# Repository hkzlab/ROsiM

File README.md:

# ROsiM - ROM simulator

## Introduction

The ROsiM is a ROM simulation / emulation board: it uses two 512k/8bit SRAM chips to simulate an 8 or 16 bit ROM (up to 512k bytes or 512k words in size).

The board is based around an ATMega328P chip @20Mhz, controlled via serial connection.

I made this out of my personal need of a simple way to quickly test ROM images on boards I repair/hack/build. Often, these boards use big 16bit EPROMs and the projects I found around did not cater to my needs.

The idea is to use this bare board and then "pods" that attach to the two 40pin header and adapt it to simulate various types of ROMs.

**WARNING:** While I might help you with quick questions, there is NOT going to be hand-holding for this one.

### Caveat Emptor!

I have currently built and tested revision 1.3 of this board. The following fixes must be implemented to make it usable:

- Wire the VCCIO pad from FT232RL to VCC and do NOT short it to 3.3v. This is already fixed in board rev. 1.4

The following mod is optional but encouraged for safety, and have been implemented for revision 1.4:

- Cut the trace between pin 1 of USB connector (Vcc) and F1, and insert a BAT48 SOD123 diode, cathode towards F1. This will protect your USB port if the board gets externally powered.
- Lower F1 max current to 200mA

## Board

This board is designed around relatively cheap through hole (with a few exceptions) components, and should be buildable by anyone with basic soldering skills.

You'll need a way to program your 328P MCU with the bootloader (you can then load the firmware via serial port).

I recommend [optiboot](https://github.com/Optiboot/optiboot). Remember to set the AVR frequency to 20Mhz and baudrate to 115200bps. I might provide prebuilt binaries of this in the future.

### Bill of Materials

**TODO**

### Connections

#### J1 - ISP 6 pin header

This is used for in-circuit programming of the MCU. You won't really use after burning the bootloader to the chip. You can leave this out if you pre-program the ATMega.

#### J2 - USB Type B female

Connect your USB cable here. It will appear as an FTDI serial port to the host.

The Interface runs at 230400bps 8-n-1. The protocol is mainly ASCII based, but meant to be used with an external software.

#### J3 - Barrel jack for power

Connect your DC power supply here, **center tip positive**.
Anything between 7 to 9V will be good, 12V will work, but the regulator might get hotter. 500mA should be enough.

#### J4 - Address header

A 40 pin header:

- Odd pins 1 thru 37 on the left side will bring out the address lines (A0-A18).
- Pin 39 will be this board's VCC.
- All even pins on the right are GND.

#### J5 - Data header

A 40 pin header: 

- Odd pins 1 thru 31 on the left side will bring out the data lines (D0-D15).
- Pin 33 will be the /CE signal input.
- Pin 35 will be the /OE signal input.
- Pin 39 will be this board's VCC.
- All even pins on the right are GND.

#### J6 - /RESET header

An active-low OC signal will be present on this header. You can use to pilot the /RESET of your target board.

Solder an arc of rigid wire on this one, so you can attach a small crocodile clip to it.

#### J7 - RESET header

An active-high signal (either high or disconnected) will be present on this header.

Solder an arc of rigid wire on this one, so you can attach a small crocodile clip to it.
## Software

While this board can be controlled directly via a simple serial terminal, it is advised to use a client software that supports the following protocol, like the [ROsiM Loader](https://github.com/hkzlab/ROsiM_Loader).

### Protocol

The **Remote Control** protocol is pretty simple and ASCII based. It supports 12 commands, each with its own syntax and response.

String `CMD_ERR` will be sent in case the command is not recognized, string `CMD_INV` will be sent in case the command cannot be executed at this time.

#### RESET

- Syntax: `>K<`
- Response: none

Forces the reset by watchdog of the ROsiM.

#### MODEL

- Syntax: `>M<`
- Response: `[M xx]`

Returns the current model of the board in hex. 

#### ADDRESS

- Syntax: `>A 00xxxxxx<`
- Response: `[A 00xxxxxx]`

Specifies the start address for the next read/write commands.
The address must be specified in hex, and a mask of 0x7FFFF will be applied to it.

#### WRITE

- Syntax: `>W xxxx<`
- Response: `[W xxxx]`

The SRAM must be in WRITE mode and the board switched to INTERNAL, otherwise the response `CMD_INV` will be sent.

`xxxx` is the data to write on SRAM at the current address in hex format.
Once the write completes, the **address will automatically increment by 1**.

#### READ

- Syntax: `>R<`
- Response: `[R xxxx]`

The SRAM must be in READ mode and the board switched to INTERNAL, otherwise the response `CMD_INV` will be sent.

`xxxx` is the data written at the current address in hex format. Once the read completes, the **address will automatically increment by 1**.

#### EXTERNAL RESET

- Syntax: `>E y<` where `y` can be `0` or `1`
- Response: `[E y]`

Enables (`1`) or disables (`0`) the external RESET signal to the target board.

#### INTERNAL/EXTERNAL SWITCH

- Syntax: `>S y<` where `y` can be `0` or `1`
- Response: `[S y]`

To execute this command, the SRAM must be in READ mode, otherwise the response `CMD_INV` will be sent.
Sets the board to INTERNAL (`1`) or EXTERNAL (`0`) mode. EXTERNAL mode will enable the drivers that communicate through the external address/data/control lines.

#### READ/WRITE SWITCH

- Syntax: `>X y<` where `y` can be `0` or `1`
- Response: `[X y]`

To execute this command, the board must be in INTERNAL mode, otherwise the response `CMD_INV` will be sent.
Sets the SRAM to READ (`1`) or WRITE (`0`) mode.

#### VIEW

- Syntax: `>V<`
- Response: `[V 00xxxxxx yy]`

This command will print out the current address in hex format (`00xxxxxx`) and a mask (`yy`) in hex format that contains:

- bit 0: INTERNAL/EXTERNAL state
- bit 1: READ/WRITE state
- bit 2: EXTERNAL RESET state

#### DEFAULTS

- Syntax: `>D<`
- Response: `[D]`

Will revert the board state to the following state:

- INTERNAL
- SRAM in READ mode
- EXTERNAL RESET disabled

The selection of the EXTERNAL RESET logic will **NOT** be restored by this command and will remain set to the current state.

#### TEST

- Syntax: `>T<`
- Response: `[T xx]`

Resets the board to defaults then executes a test on the SRAMs by writing patterns of data in them and reading them back.

The output can be:

- `00` test was completed successfully
- `01` test failed while writing the first pattern (`0xAA55`)
- `02` test failed while writing the first pattern (`0x55AA`)
- `03` the test failed while writing the incremental pattern

#### XMODEM

- Syntax: `>O x<`
- Response: `[O yy]`

Starts an XMODEM transfer of a binary file into the SRAM.

`x` can be:

- `0` The file will be considered an 8-bit dump, the highest 8 bits of the SRAM will be set to `0x00`, only the lower 8 bits will be set.
- `1` The file will be considered a 16-bit dump, and the data will be loaded into the SRAM in words. ODD bytes in the dump will end up in the high byte of the SRAM, EVEN bytes will end up in the low byte of the SRAM.
- `2` The file will be considered a **byte swapped** 16-bit dump, and the data will be loaded into the SRAM in words. EVEN bytes in the dump will end up in the high byte of the SRAM, ODD bytes will end up in the low byte of the SRAM.

`yy` will be:

- `00` for a failed transfer.
- `01` for a successful transfer.

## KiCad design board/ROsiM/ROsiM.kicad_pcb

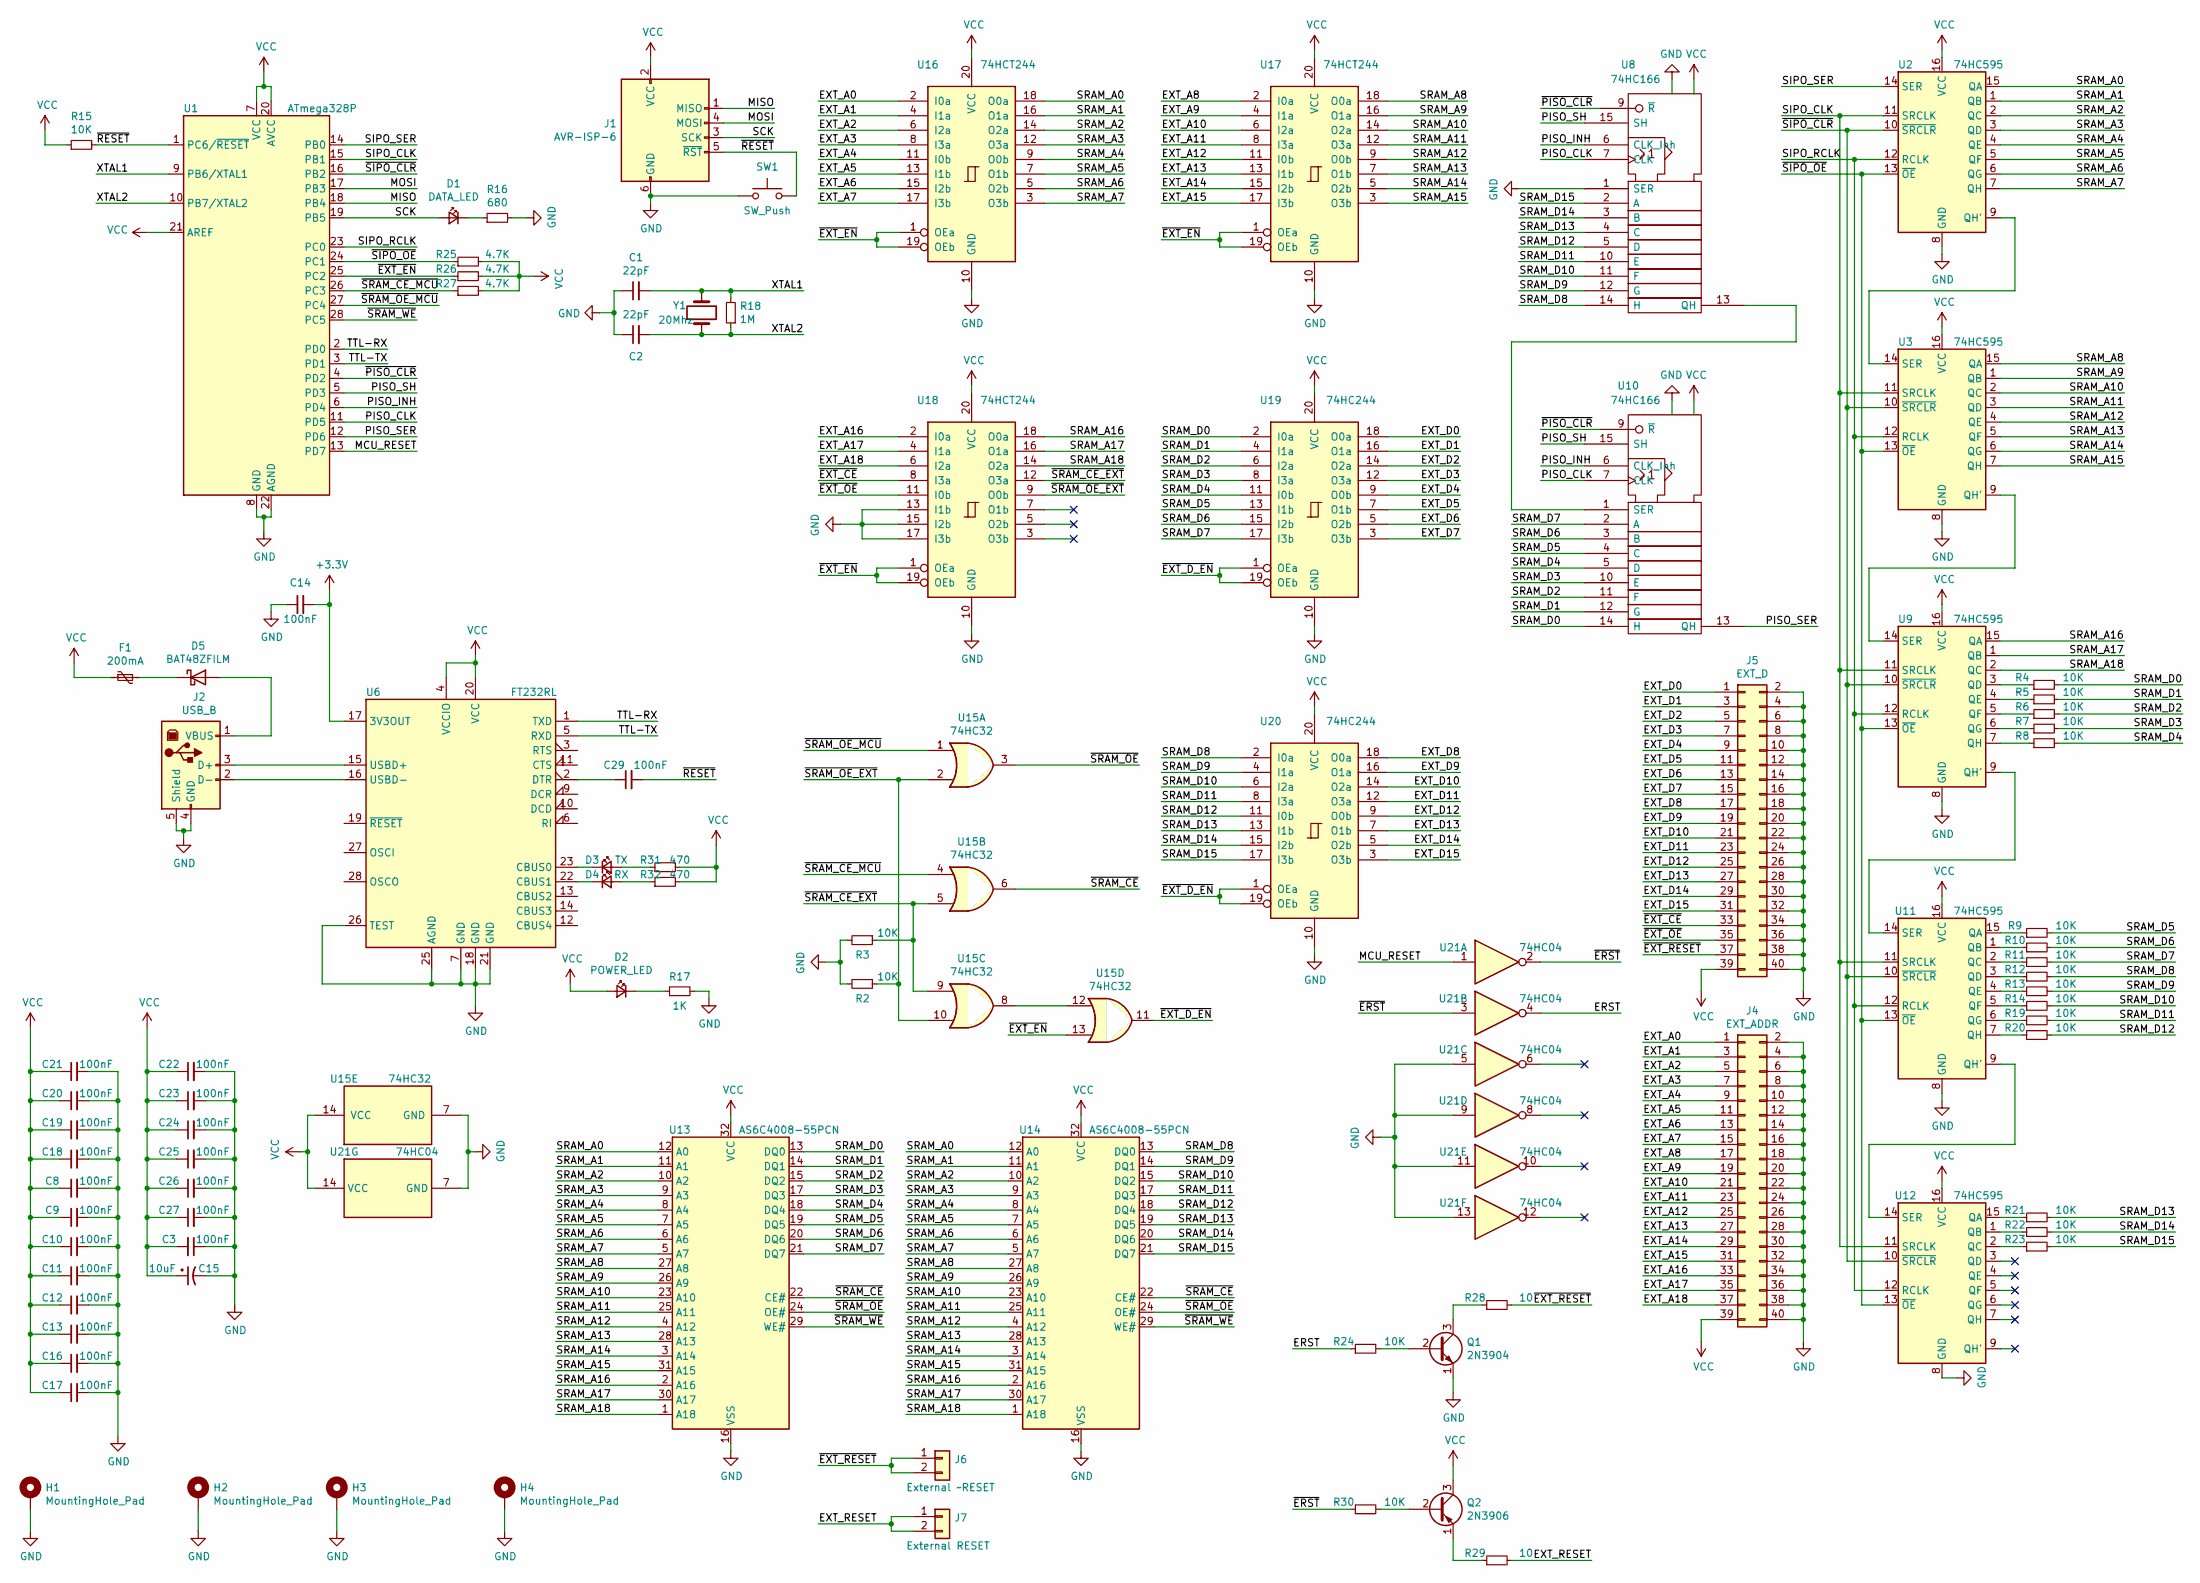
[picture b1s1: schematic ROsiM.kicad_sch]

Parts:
C1, C2: 22pF; C_Disc_D3.0mm_W2.0mm_P2.50mm
C3, C8, C9, C10, C11, C12, C13, C14, C16, C17, C18, C19, C20, C21, C22, C23, C24, C25, C26, C27, C29: 100nF; C_Disc_D3.4mm_W2.1mm_P2.50mm
C15: 10uF; CP_Radial_D5.0mm_P2.50mm
D1: DATA_LED; LED_D2.0mm_W4.8mm_H2.5mm_FlatTop
D2: POWER_LED; LED_D2.0mm_W4.8mm_H2.5mm_FlatTop
D3: TX; LED_D2.0mm_W4.8mm_H2.5mm_FlatTop
D4: RX; LED_D2.0mm_W4.8mm_H2.5mm_FlatTop
D5: BAT48ZFILM; D_SOD-123
F1: 200mA; Fuse_1206_3216Metric
H1, H2, H3, H4: MountingHole_Pad; MountingHole_2.7mm_M2.5_ISO7380_Pad
J1: AVR-ISP-6; IDC-Header_2x03_P2.54mm_Vertical
J2: USB_B; USB_B_Lumberg_2411_02_Horizontal
J4: EXT_ADDR; PinHeader_2x20_P2.54mm_Vertical
J5: EXT_D; PinHeader_2x20_P2.54mm_Vertical
J6: External ~RESET; PinSocket_1x02_P2.54mm_Vertical
J7: External RESET; PinSocket_1x02_P2.54mm_Vertical
Q1: 2N3904; TO-92_Inline
Q2: 2N3906; TO-92_Inline
R2, R3, R4, R5, R6, R7, R8, R9, R10, R11, R12, R13, R14, R15, R19, R20, R21, R22, R23, R24, R30: 10K; R_Axial_DIN0204_L3.6mm_D1.6mm_P7.62mm_Horizontal
R16: 680; R_Axial_DIN0204_L3.6mm_D1.6mm_P7.62mm_Horizontal
R17: 1K; R_Axial_DIN0204_L3.6mm_D1.6mm_P7.62mm_Horizontal
R18: 1M; R_Axial_DIN0204_L3.6mm_D1.6mm_P7.62mm_Horizontal
R25, R26, R27: 4.7K; R_Axial_DIN0204_L3.6mm_D1.6mm_P7.62mm_Horizontal
R28, R29: 10; R_Axial_DIN0204_L3.6mm_D1.6mm_P7.62mm_Horizontal
R31, R32: 470; R_Axial_DIN0204_L3.6mm_D1.6mm_P7.62mm_Horizontal
SW1: SW_Push; SW_PUSH_6mm
U1: ATmega328P; DIP-28_W7.62mm
U2, U3, U9, U11, U12: 74HC595; DIP-16_W7.62mm
U6: FT232RL; SSOP-28_5.3x10.2mm_P0.65mm
U8, U10: 74HC166; DIP-16_W7.62mm
U13, U14: AS6C4008-55PCN; DIP-32_W15.24mm
U15: 74HC32; DIP-14_W7.62mm
U16, U17, U18: 74HCT244; DIP-20_W7.62mm
U19, U20: 74HC244; DIP-20_W7.62mm
U21: 74HC04; DIP-14_W7.62mm
Y1: 20Mhz; Crystal_HC49-U_Vertical

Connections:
+3V3: C14.2, U6.17 (3V3OUT)
/ERST: R24.1, U21.4
/EXT_A0: J4.1, U16.2 (I0a)
/EXT_A1: J4.3, U16.4 (I1a)
/EXT_A2: J4.5, U16.6 (I2a)
/EXT_A3: J4.7, U16.8 (I3a)
/EXT_A4: J4.9, U16.11 (I0b)
/EXT_A5: J4.11, U16.13 (I1b)
/EXT_A6: J4.13, U16.15 (I2b)
/EXT_A7: J4.15, U16.17 (I3b)
/EXT_A8: J4.17, U17.2 (I0a)
/EXT_A9: J4.19, U17.4 (I1a)
/EXT_A10: J4.21, U17.6 (I2a)
/EXT_A11: J4.23, U17.8 (I3a)
/EXT_A12: J4.25, U17.11 (I0b)
/EXT_A13: J4.27, U17.13 (I1b)
/EXT_A14: J4.29, U17.15 (I2b)
/EXT_A15: J4.31, U17.17 (I3b)
/EXT_A16: J4.33, U18.2 (I0a)
/EXT_A17: J4.35, U18.4 (I1a)
/EXT_A18: J4.37, U18.6 (I2a)
/EXT_D0: J5.1, U19.18 (O0a)
/EXT_D1: J5.3, U19.16 (O1a)
/EXT_D2: J5.5, U19.14 (O2a)
/EXT_D3: J5.7, U19.12 (O3a)
/EXT_D4: J5.9, U19.9 (O0b)
/EXT_D5: J5.11, U19.7 (O1b)
/EXT_D6: J5.13, U19.5 (O2b)
/EXT_D7: J5.15, U19.3 (O3b)
/EXT_D8: J5.17, U20.18 (O0a)
/EXT_D9: J5.19, U20.16 (O1a)
/EXT_D10: J5.21, U20.14 (O2a)
/EXT_D11: J5.23, U20.12 (O3a)
/EXT_D12: J5.25, U20.9 (O0b)
/EXT_D13: J5.27, U20.7 (O1b)
/EXT_D14: J5.29, U20.5 (O2b)
/EXT_D15: J5.31, U20.3 (O3b)
/EXT_RESET: J7.1, J7.2, R29.2
/MCU_RESET: U1.13 (PD7), U21.1
/MISO: J1.1 (MISO), U1.18 (PB4)
/MOSI: J1.4 (MOSI), U1.17 (PB3)
/PISO_CLK: U1.11 (PD5), U8.7 (CLK), U10.7 (CLK)
/PISO_INH: U1.6 (PD4), U8.6 (CLK_Inh), U10.6 (CLK_Inh)
/PISO_SER: U1.12 (PD6), U10.13 (QH)
/PISO_SH: U1.5 (PD3), U8.15 (SH), U10.15 (SH)
/SCK: D1.2 (A), J1.3 (SCK), U1.19 (PB5)
/SIPO_CLK: U1.15 (PB1), U2.11 (SRCLK), U3.11 (SRCLK), U9.11 (SRCLK), U11.11 (SRCLK), U12.11 (SRCLK)
/SIPO_RCLK: U1.23 (PC0), U2.12 (RCLK), U3.12 (RCLK), U9.12 (RCLK), U11.12 (RCLK), U12.12 (RCLK)
/SIPO_SER: U1.14 (PB0), U2.14 (SER)
/SRAM_A0: U2.15 (QA), U13.12 (A0), U14.12 (A0), U16.18 (O0a)
/SRAM_A1: U2.1 (QB), U13.11 (A1), U14.11 (A1), U16.16 (O1a)
/SRAM_A2: U2.2 (QC), U13.10 (A2), U14.10 (A2), U16.14 (O2a)
/SRAM_A3: U2.3 (QD), U13.9 (A3), U14.9 (A3), U16.12 (O3a)
/SRAM_A4: U2.4 (QE), U13.8 (A4), U14.8 (A4), U16.9 (O0b)
/SRAM_A5: U2.5 (QF), U13.7 (A5), U14.7 (A5), U16.7 (O1b)
/SRAM_A6: U2.6 (QG), U13.6 (A6), U14.6 (A6), U16.5 (O2b)
/SRAM_A7: U2.7 (QH), U13.5 (A7), U14.5 (A7), U16.3 (O3b)
/SRAM_A8: U3.15 (QA), U13.27 (A8), U14.27 (A8), U17.18 (O0a)
/SRAM_A9: U3.1 (QB), U13.26 (A9), U14.26 (A9), U17.16 (O1a)
/SRAM_A10: U3.2 (QC), U13.23 (A10), U14.23 (A10), U17.14 (O2a)
/SRAM_A11: U3.3 (QD), U13.25 (A11), U14.25 (A11), U17.12 (O3a)
/SRAM_A12: U3.4 (QE), U13.4 (A12), U14.4 (A12), U17.9 (O0b)
/SRAM_A13: U3.5 (QF), U13.28 (A13), U14.28 (A13), U17.7 (O1b)
/SRAM_A14: U3.6 (QG), U13.3 (A14), U14.3 (A14), U17.5 (O2b)
/SRAM_A15: U3.7 (QH), U13.31 (A15), U14.31 (A15), U17.3 (O3b)
/SRAM_A16: U9.15 (QA), U13.2 (A16), U14.2 (A16), U18.18 (O0a)
/SRAM_A17: U9.1 (QB), U13.30 (A17), U14.30 (A17), U18.16 (O1a)
/SRAM_A18: U9.2 (QC), U13.1 (A18), U14.1 (A18), U18.14 (O2a)
/SRAM_D0: R4.2, U10.14 (H), U13.13 (DQ0), U19.2 (I0a)
/SRAM_D1: R5.2, U10.12 (G), U13.14 (DQ1), U19.4 (I1a)
/SRAM_D2: R6.2, U10.11 (F), U13.15 (DQ2), U19.6 (I2a)
/SRAM_D3: R7.2, U10.10 (E), U13.17 (DQ3), U19.8 (I3a)
/SRAM_D4: R8.2, U10.5 (D), U13.18 (DQ4), U19.11 (I0b)
/SRAM_D5: R9.2, U10.4 (C), U13.19 (DQ5), U19.13 (I1b)
/SRAM_D6: R10.2, U10.3 (B), U13.20 (DQ6), U19.15 (I2b)
/SRAM_D7: R11.2, U10.2 (A), U13.21 (DQ7), U19.17 (I3b)
/SRAM_D8: R12.2, U8.14 (H), U14.13 (DQ0), U20.2 (I0a)
/SRAM_D9: R13.2, U8.12 (G), U14.14 (DQ1), U20.4 (I1a)
/SRAM_D10: R14.2, U8.11 (F), U14.15 (DQ2), U20.6 (I2a)
/SRAM_D11: R19.2, U8.10 (E), U14.17 (DQ3), U20.8 (I3a)
/SRAM_D12: R20.2, U8.5 (D), U14.18 (DQ4), U20.11 (I0b)
/SRAM_D13: R21.2, U8.4 (C), U14.19 (DQ5), U20.13 (I1b)
/SRAM_D14: R22.2, U8.3 (B), U14.20 (DQ6), U20.15 (I2b)
/SRAM_D15: R23.2, U8.2 (A), U14.21 (DQ7), U20.17 (I3b)
/TTL-RX: U1.2 (PD0), U6.1 (TXD)
/TTL-TX: U1.3 (PD1), U6.5 (RXD)
/XTAL1: C1.2, R18.2, U1.9 (PB6/XTAL1), Y1.2
/XTAL2: C2.2, R18.1, U1.10 (PB7/XTAL2), Y1.1
/~ERST: R30.1, U21.2, U21.3
/~EXT_CE: J5.33, U18.8 (I3a)
/~EXT_D_EN: U15.11, U19.1 (OEa), U19.19 (OEb), U20.1 (OEa), U20.19 (OEb)
/~EXT_EN: R26.1, U1.25 (PC2), U15.13, U16.1 (OEa), U16.19 (OEb), U17.1 (OEa), U17.19 (OEb), U18.1 (OEa), U18.19 (OEb)
/~EXT_OE: J5.35, U18.11 (I0b)
/~EXT_RESET: J5.37, J6.1, J6.2, R28.2
/~PISO_CLR: U1.4 (PD2), U8.9 (~R), U10.9 (~R)
/~RESET: C29.2, J1.5 (~RST), R15.2, SW1.2, U1.1 (PC6/~RESET)
/~SIPO_CLR: U1.16 (PB2), U2.10 (~SRCLR), U3.10 (~SRCLR), U9.10 (~SRCLR), U11.10 (~SRCLR), U12.10 (~SRCLR)
/~SIPO_OE: R25.1, U1.24 (PC1), U2.13 (~OE), U3.13 (~OE), U9.13 (~OE), U11.13 (~OE), U12.13 (~OE)
/~SRAM_CE_EXT: R3.1, U15.5, U15.9, U18.12 (O3a)
/~SRAM_CE_MCU: R27.1, U1.26 (PC3), U15.4
/~SRAM_CE: U13.22 (CE#), U14.22 (CE#), U15.6
/~SRAM_OE_EXT: R2.1, U15.2, U15.10, U18.9 (O0b)
/~SRAM_OE_MCU: U1.27 (PC4), U15.1
/~SRAM_OE: U13.24 (OE#), U14.24 (OE#), U15.3
/~SRAM_WE: U1.28 (PC5), U13.29 (WE#), U14.29 (WE#)
GND: C1.1, C2.1, C3.1, C8.2, C9.2, C10.2, C11.2, C12.2, C13.2, C14.1, C15.2, C16.2, C17.2, C18.2, C19.2, C20.2, C21.2, C22.2, C23.2, C24.2, C25.2, C26.2, C27.2, H1.1, H2.1, H3.1, H4.1, J1.6 (GND), J2.4 (GND), J2.5 (Shield), J4.2, J4.4, J4.6, J4.8, J4.10, J4.12, J4.14, J4.16, J4.18, J4.20, J4.22, J4.24, J4.26, J4.28, J4.30, J4.32, J4.34, J4.36, J4.38, J4.40, J5.2, J5.4, J5.6, J5.8, J5.10, J5.12, J5.14, J5.16, J5.18, J5.20, J5.22, J5.24, J5.26, J5.28, J5.30, J5.32, J5.34, J5.36, J5.38, J5.40, Q1.1 (E), R2.2, R3.2, R16.2, R17.2, SW1.1, U1.8 (GND), U1.22 (AGND), U2.8 (GND), U3.8 (GND), U6.7 (GND), U6.18 (GND), U6.21 (GND), U6.25 (AGND), U6.26 (TEST), U8.1 (SER), U8.8 (GND), U9.8 (GND), U10.8 (GND), U11.8 (GND), U12.8 (GND), U13.16 (VSS), U14.16 (VSS), U15.7 (GND), U16.10 (GND), U17.10 (GND), U18.10 (GND), U18.13 (I1b), U18.15 (I2b), U18.17 (I3b), U19.10 (GND), U20.10 (GND), U21.5, U21.7 (GND), U21.9, U21.11, U21.13
unnamed: C29.1, U6.2 (DTR)
unnamed: D1.1 (K), R16.1
unnamed: D2.1 (K), R17.1
unnamed: D3.1 (K), U6.23 (CBUS0)
unnamed: D3.2 (A), R31.1
unnamed: D4.1 (K), U6.22 (CBUS1)
unnamed: D4.2 (A), R32.1
unnamed: D5.1 (K), F1.2
unnamed: D5.2 (A), J2.1 (VBUS)
unnamed: J2.2 (D-), U6.16 (USBD-)
unnamed: J2.3 (D+), U6.15 (USBD+)
unnamed: Q1.2 (B), R24.2
unnamed: Q1.3 (C), R28.1
unnamed: Q2.1 (E), R29.1
unnamed: Q2.2 (B), R30.2
unnamed: R4.1, U9.3 (QD)
unnamed: R5.1, U9.4 (QE)
unnamed: R6.1, U9.5 (QF)
unnamed: R7.1, U9.6 (QG)
unnamed: R8.1, U9.7 (QH)
unnamed: R9.1, U11.15 (QA)
unnamed: R10.1, U11.1 (QB)
unnamed: R11.1, U11.2 (QC)
unnamed: R12.1, U11.3 (QD)
unnamed: R13.1, U11.4 (QE)
unnamed: R14.1, U11.5 (QF)
unnamed: R19.1, U11.6 (QG)
unnamed: R20.1, U11.7 (QH)
unnamed: R21.1, U12.15 (QA)
unnamed: R22.1, U12.1 (QB)
unnamed: R23.1, U12.2 (QC)
unnamed: U2.9 (QH'), U3.14 (SER)
unnamed: U3.9 (QH'), U9.14 (SER)
unnamed: U8.13 (QH), U10.1 (SER)
unnamed: U11.9 (QH'), U12.14 (SER)
unnamed: U9.9 (QH'), U11.14 (SER)
unnamed: U15.8, U15.12
VCC: C3.2, C8.1, C9.1, C10.1, C11.1, C12.1, C13.1, C15.1, C16.1, C17.1, C18.1, C19.1, C20.1, C21.1, C22.1, C23.1, C24.1, C25.1, C26.1, C27.1, D2.2 (A), F1.1, J1.2 (VCC), J4.39, J5.39, Q2.3 (C), R15.1, R25.2, R26.2, R27.2, R31.2, R32.2, U1.7 (VCC), U1.20 (AVCC), U1.21 (AREF), U2.16 (VCC), U3.16 (VCC), U6.4 (VCCIO), U6.20 (VCC), U8.16 (VCC), U9.16 (VCC), U10.16 (VCC), U11.16 (VCC), U12.16 (VCC), U13.32 (VCC), U14.32 (VCC), U15.14 (VCC), U16.20 (VCC), U17.20 (VCC), U18.20 (VCC), U19.20 (VCC), U20.20 (VCC), U21.14 (VCC)

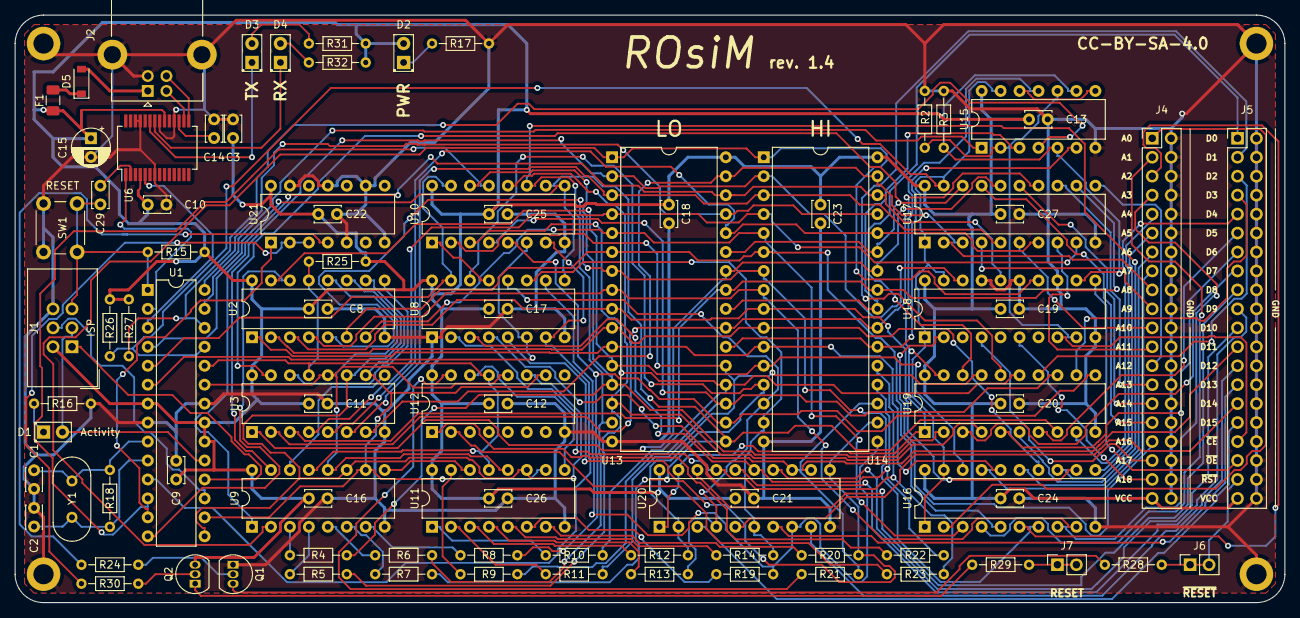
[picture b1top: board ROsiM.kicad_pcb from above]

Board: 2 copper layers, 170.2 x 78.7 mm, 93 parts (0 on the bottom side), 144 nets.

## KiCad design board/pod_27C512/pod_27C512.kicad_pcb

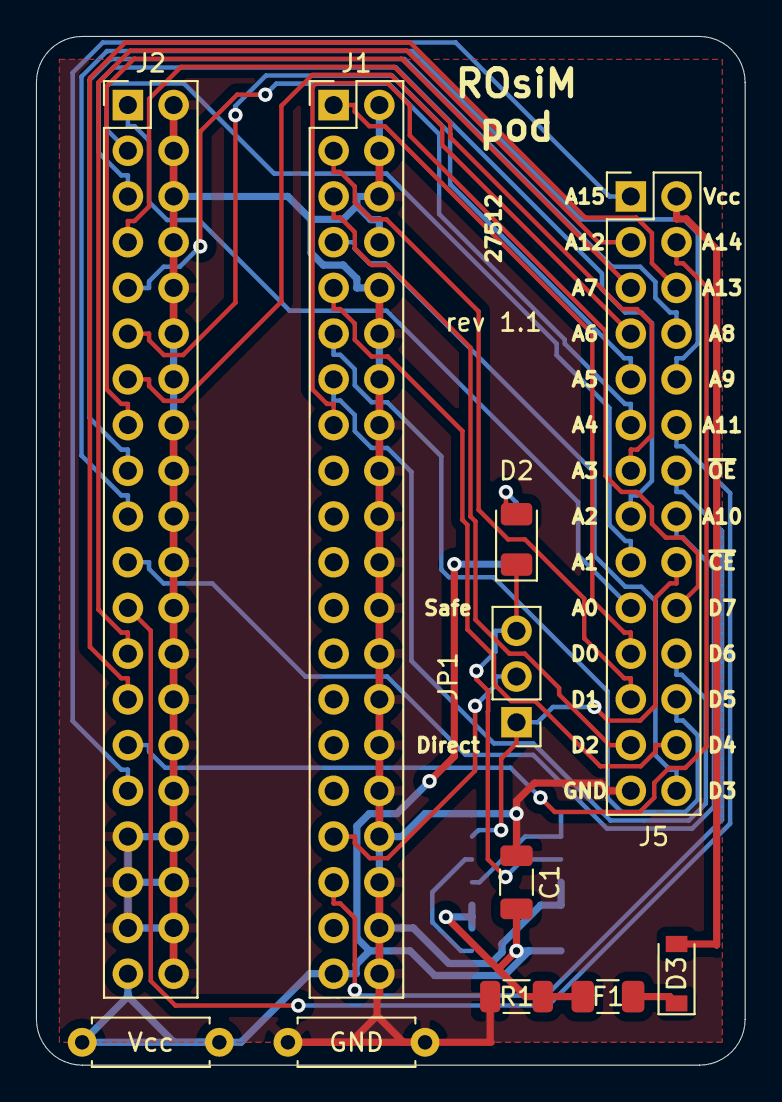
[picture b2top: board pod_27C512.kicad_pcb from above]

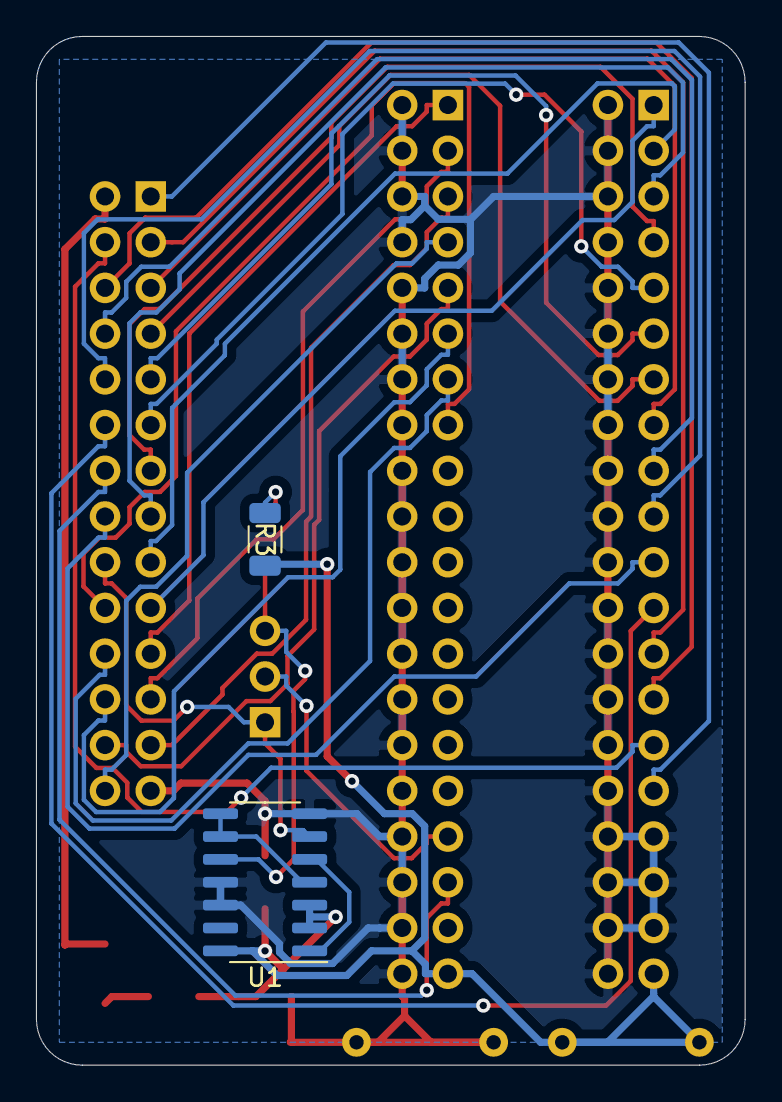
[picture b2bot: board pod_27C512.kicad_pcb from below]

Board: 2 copper layers, 39.4 x 57.2 mm, 13 parts (2 on the bottom side), 35 nets.

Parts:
C1: 100nF; C_1206_3216Metric
D2: GREEN; LED_1206_3216Metric
D3: BAT48ZFILM; D_SOD-123
F1: 200mA; Fuse_1206_3216Metric
J1: EXT_D; PinHeader_2x20_P2.54mm_Vertical
J2: EXT_ADDR; PinHeader_2x20_P2.54mm_Vertical
J3: VCC_Probe; R_Axial_DIN0207_L6.3mm_D2.5mm_P7.62mm_Horizontal
J4: GND_Probe; R_Axial_DIN0207_L6.3mm_D2.5mm_P7.62mm_Horizontal
J5: ROM Lines; PinHeader_2x14_P2.54mm_Vertical
JP1: /OE Selection; PinHeader_1x03_P2.54mm_Vertical
R1: 4.7K; R_1206_3216Metric
R3: 470; R_1206_3216Metric
U1: 74HCT02; SO-14_3.9x8.65mm_P1.27mm

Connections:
/A0: J2.1, J5.19
/A1: J2.3, J5.17
/A2: J2.5, J5.15
/A3: J2.7, J5.13
/A4: J2.9, J5.11
/A5: J2.11, J5.9
/A6: J2.13, J5.7
/A7: J2.15, J5.5
/A8: J2.17, J5.8
/A9: J2.19, J5.10
/A10: J2.21, J5.16
/A11: J2.23, J5.12
/A12: J2.25, J5.3
/A13: J2.27, J5.6
/A14: J2.29, J5.4
/A15: J2.31, J5.1
/D0: J1.1, J5.21
/D1: J1.3, J5.23
/D2: J1.5, J5.25
/D3: J1.7, J5.28
/D4: J1.9, J5.26
/D5: J1.11, J5.24
/D6: J1.13, J5.22
/D7: J1.15, J5.20
/~B_CE: J1.33, JP1.2
/~DIR_CE: J5.18, JP1.1, U1.6
/~OE: J1.35, J5.14
/~SAFE_CE: D2.1, JP1.3, U1.10
GND: C1.1, J1.2, J1.4, J1.6, J1.8, J1.10, J1.12, J1.14, J1.16, J1.18, J1.20, J1.22, J1.24, J1.26, J1.28, J1.30, J1.32, J1.34, J1.36, J1.38, J1.40, J2.2, J2.4, J2.6, J2.8, J2.10, J2.12, J2.14, J2.16, J2.18, J2.20, J2.22, J2.24, J2.26, J2.28, J2.30, J2.32, J2.33, J2.34, J2.35, J2.36, J2.37, J2.38, J2.40, J4.1, J4.2, J5.27, R1.1, U1.7, U1.11, U1.12
unnamed: D2.2, R3.1
unnamed: D3.1, F1.1
unnamed: D3.2, J5.2
unnamed: U1.1, U1.5
unnamed: U1.4, U1.8, U1.9
VCC: C1.2, F1.2, J1.39, J2.39, J3.1, J3.2, R1.2, R3.2, U1.2, U1.3, U1.14

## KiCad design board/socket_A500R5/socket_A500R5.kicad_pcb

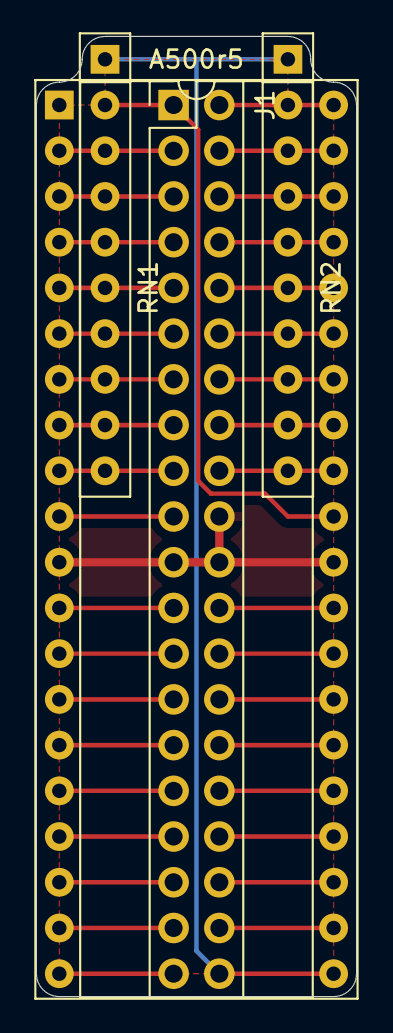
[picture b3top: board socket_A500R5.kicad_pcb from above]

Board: 2 copper layers, 17.8 x 53.3 mm, 4 parts (0 on the bottom side), 38 nets.

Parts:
A500r5: A500 R5; DIP-40_W15.24mm_Socket
J1: Adapter; PinHeader_2x20_P2.54mm_Vertical
RN1, RN2: 4k7; R_Array_SIP10

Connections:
/A0: A500r5.9, J1.17, RN1.10
/A1: A500r5.8, J1.15, RN1.9
/A2: A500r5.7, J1.13, RN1.8
/A3: A500r5.6, J1.11, RN1.7
/A4: A500r5.5, J1.9, RN1.6
/A5: A500r5.4, J1.7, RN1.5
/A6: A500r5.3, J1.5, RN1.4
/A7: A500r5.2, J1.3, RN1.3
/A8: A500r5.40, J1.2, RN2.2
/A9: A500r5.39, J1.4, RN2.3
/A10: A500r5.38, J1.6, RN2.4
/A11: A500r5.37, J1.8, RN2.5
/A12: A500r5.36, J1.10, RN2.6
/A13: A500r5.35, J1.12, RN2.7
/A14: A500r5.34, J1.14, RN2.8
/A15: A500r5.33, J1.16, RN2.9
/A16: A500r5.32, J1.18, RN2.10
/A17: A500r5.31, J1.1, RN1.2
/D0: A500r5.13, J1.25
/D1: A500r5.15, J1.29
/D2: A500r5.17, J1.33
/D3: A500r5.19, J1.37
/D4: A500r5.22, J1.38
/D5: A500r5.24, J1.34
/D6: A500r5.26, J1.30
/D7: A500r5.28, J1.26
/D8: A500r5.14, J1.27
/D9: A500r5.16, J1.31
/D10: A500r5.18, J1.35
/D11: A500r5.20, J1.39
/D12: A500r5.23, J1.36
/D13: A500r5.25, J1.32
/D14: A500r5.27, J1.28
/D15: A500r5.29, J1.24
/EXT_VCC: A500r5.21, J1.40, RN1.1, RN2.1
/~CE: A500r5.10, J1.19
/~OE: A500r5.12, J1.23
GND: A500r5.11, A500r5.30, J1.20, J1.21, J1.22

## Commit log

2020-10-28 Basic files
2020-10-28 Add caps
2020-10-28 Add resistors to SIPO shifter for data out
2020-10-28 Add external reset code
2020-10-28 Fix multiple D3
2020-10-28 Add external connector
2020-10-28 Add some footprints
2020-10-28 Rename
2020-10-28 Make sure the Dout xcvers are disabled when the ROM is not selected
2020-10-28 Add resistor on the reset line
2020-10-28 Add transistor for OC reset output
2020-10-28 Move around some components
2020-10-28 Begin drawing the PCB
2020-10-29 Begin organizing ROsiM board
2020-10-29 Begin routing traces
2020-10-29 Complete routing
2020-10-29 Update PCB
2020-10-29 Fix solder mask issue
2020-10-30 Add pull-up to disable drivers and shifters
2020-10-30 Added another resitor for SRAM CE
2020-10-30 Add resistors to pullup sram selection
2020-11-13 Begin importing code from DuPAL
2020-11-13 Begin changes in DuPAL code
2020-11-13 begin adding more io defines
2020-11-13 Cleaned up the protocol and implemented the initialization
2020-11-13 Removed other unused pin initializations
2020-11-13 Removed call to unexisting ioutils_write
2020-11-14 Begin defining commands for remote control
2020-11-14 Begin implementing commands
2020-11-14 Begin setting up the initial state for IOs
2020-11-14 Fix string print for VIEW command
2020-11-14 Begin implementing code for commands
2020-11-14 Add more code to commands
2020-11-14 Add another command
2020-11-14 Adding more commands
2020-11-14 More commands
2020-11-14 More changes on the switch between external and internal
2020-11-14 Fix if condition
2020-11-14 Fix address to sipo buffer
2020-11-14 Fix u16 string formatting
2020-11-14 Additional comments
2020-11-14 Remove unused code and add more checks on external mode
2020-11-14 fix reset default state
2020-11-14 Invert reset parameters
2020-11-15 Add default command and begin adding test command
2020-11-15 Added basic test
2020-11-15 fixed address to buffer masks
2020-11-15 Changed some debug strings
2020-11-15 Optimize test code print a bit
2020-11-16 Comments
2020-11-16 Automatic address increment when we read or write
2020-11-17 Added TODOs
2020-11-17 Add pod and update TODO
2020-11-17 Update first pod schematics
2020-11-17 Update pod project
2020-11-18 Add delays during IO switch to make sure there are no conflicts
2020-11-18 Make sure WE is not enabled if switching board from int to ext
2020-11-19 Update TODOs
2020-11-19 Add socket for 27C512
2020-11-19 Add crc code
2020-11-19 Rev 1.1 of the board, and initial readme
2020-11-19 move licences
2020-11-19 Edited the README
2020-11-19 Added board PDF
2020-11-19 empty functions for xmodem
2020-11-19 Begin implementing xmodem
2020-11-19 untested code for xmodem
2020-11-19 Begin wiring up the xfer table
2020-11-19 Add a newline after the execution of xmodem
2020-11-19 Fix first implementation for xmodem
2020-11-20 Add timeouts to xmodem transfer
2020-11-20 simplify xmodem command
2020-11-20 Send NACK with a timeout fail
2020-11-20 move code to handle the sipo buffer out of remote control
2020-11-20 Handle xmodem packet retransmission
2020-11-20 add SRAM upload code via xmodem
2020-11-20 reduce delay in sipo shifters
2020-11-20 Further reduce delays for sipo and RAM
2020-11-20 bump version
2020-11-20 Begin filling the README
2020-11-20 Add basic description
2020-11-20 Add more README description
2020-11-20 More README!
2020-11-20 Small fix in README
2020-11-20 Added gerbers for rev 1.1
2020-11-20 README updates
2020-11-20 Fix protocol in README
2020-11-21 Reduce delays when running the SRAM test
2020-11-21 Remove useless var and fix multiple definition of same var
2020-11-21 fix typo
2020-11-21 Add 27C256 socket
2020-11-21 Add sockets for 27C32 and 64
2020-11-21 Add 2716 socket
2020-11-21 Add pod for 27040
2020-11-21 Added pod for 27C400, modified other pods
2020-11-21 Add 27C400/16 socket
2020-11-21 Add 27C400 / 8 bit mode socket
2020-11-21 Add socket for 27C020 and 27C040
2020-11-21 Added a500 socket
2020-11-22 Force the board in a safe state when we're forcing a reset
2020-11-22 Force unused address lines to low for 27C512 pod
2020-11-22 Updated TODO
2020-11-22 Add code to invert reset logic, uniform reset parameter with the rest
2020-11-22 the set_defaults functions now can exclude the reset line
2020-11-22 Change target name
2020-11-23 Renamed ROsiM board
2020-11-23 Updating for 1.2 PCB
2020-11-23 Remove support for reset inversion, obsolete with rev 1.2
2020-11-24 Begin designing rev 1.3
2020-11-24 Add rev 1.3 design
2020-11-24 Updated readme and 1.3 pcb
2020-11-24 Whoops, a cap was inverted
2020-11-24 Update picture
2020-11-27 Update the schematics
2020-11-27 Added errata
2020-11-27 Add gerbers for boards
2020-11-30 Lowered the delays
2020-11-30 Updated speed for serial connection to 500k
2020-11-30 No need to use 16bit values
2020-11-30 no need to use an int for a 4 bit value...
2020-11-30 Reduce baudrate to avoid issues with some adapters
2020-11-30 Optimize build, replace function with macro
2020-11-30 Slow down PISO access a bit to avoid potential timing issues
2020-12-01 use a specific define for a triple "nop"
2020-12-02 Use single method to fill sipo buffer
2020-12-02 optimize generating the the sipo buffer
2020-12-02 remove unised proto
2020-12-02 unroll loops in fill_sipo_buffer, as it gives a good speed boost
2020-12-12 Update the 27C512 pod by adding a protection diode
2020-12-12 Update all the pods to include the diode
2020-12-13 Update ROsiM design
2021-01-21 Added schottky diode on USB +5v input
2021-01-21 Lower specification of F1 to 200mA, to stay under BAT48 max current
2021-01-21 Update 27C040 pod
2021-01-21 Update 27C400 Pod
2021-01-21 Update 27C512 pod
2021-11-09 Update KiCad URL
2023-12-22 Add cache files
2023-12-22 Update part of the project for kicad 7

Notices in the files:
board/ROsiM/ROsiM.kicad_pcb:
CC-BY-SA-4.0
